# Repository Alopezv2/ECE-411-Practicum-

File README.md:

# ECE-411-Practicum-Skynet-2020

The Future in Artificial Intelligence 

The following Repo consits of the firmware, PCB layout, schematic and more
resources used to build and complete the project.

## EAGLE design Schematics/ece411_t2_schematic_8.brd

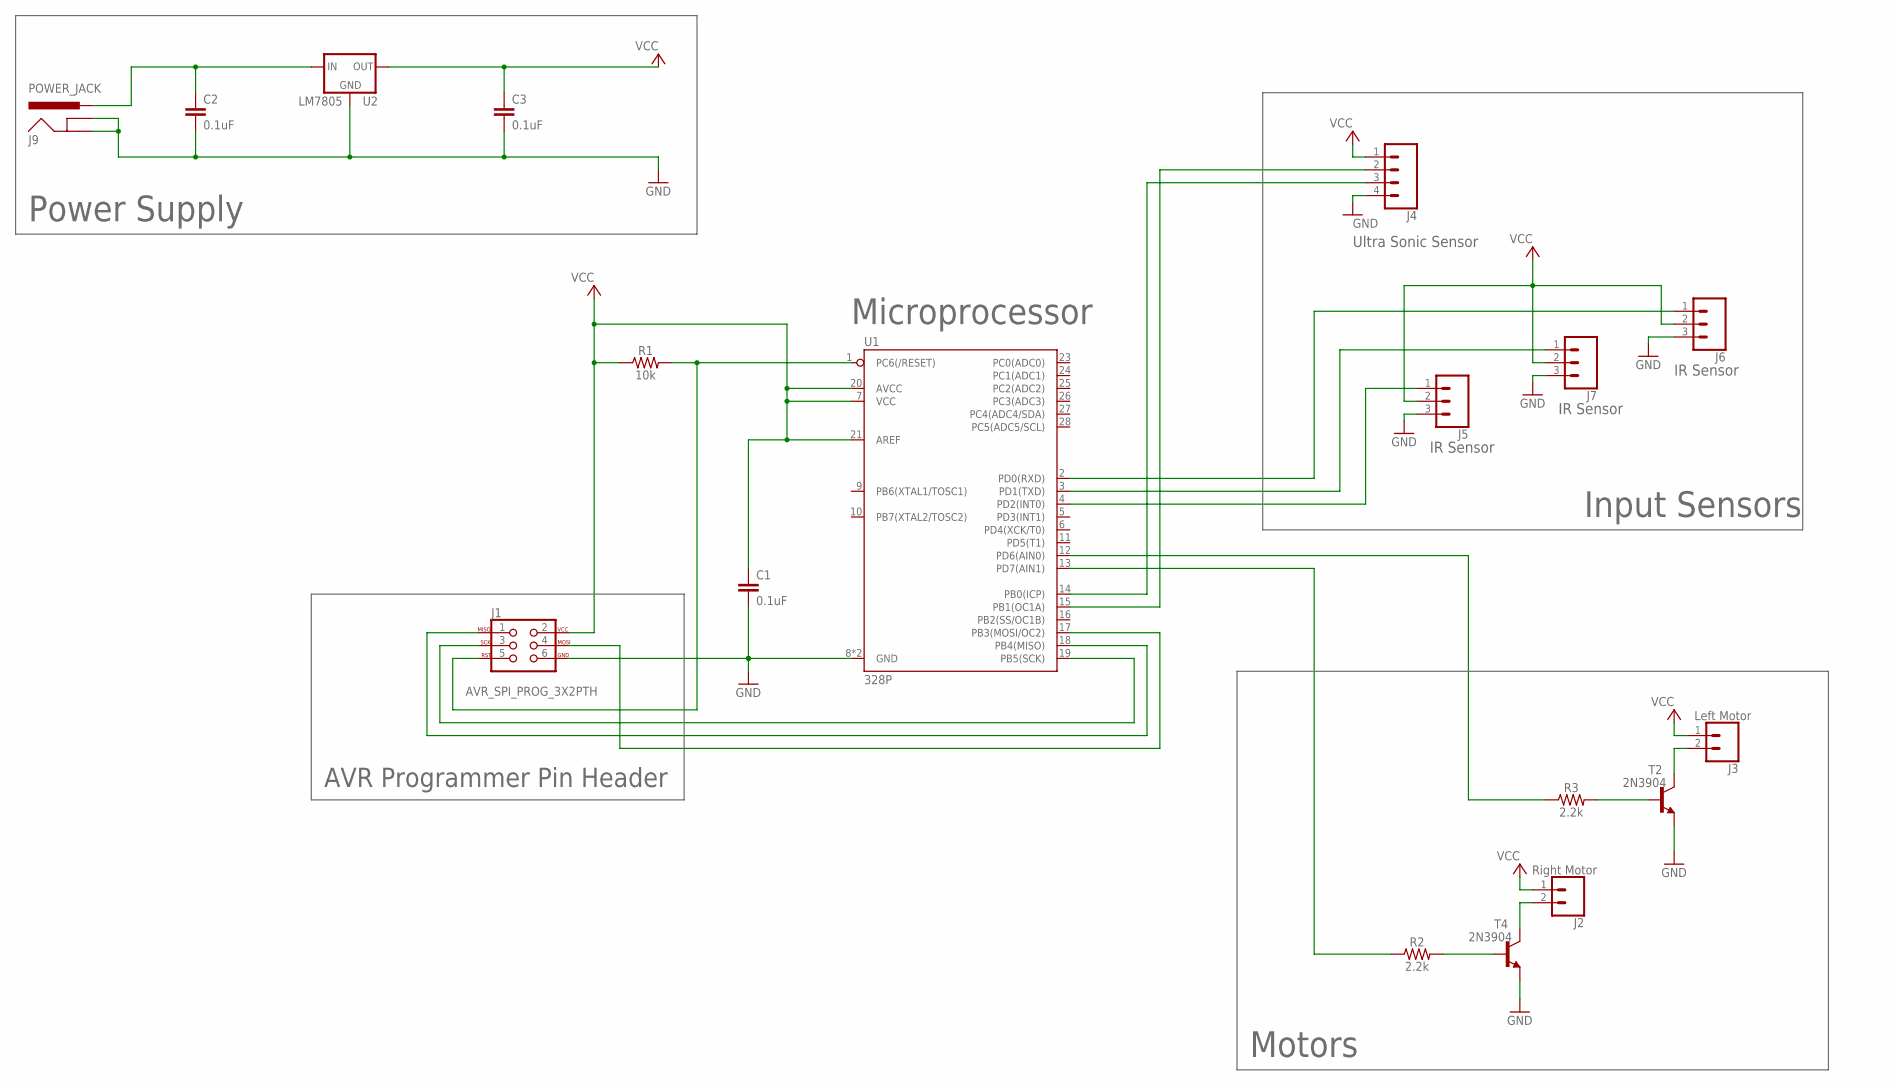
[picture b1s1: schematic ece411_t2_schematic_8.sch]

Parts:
C1, C2, C3: 0.1uF; 0402
J1: AVR_SPI_PROG_3X2PTH; 2X3
J2: Right Motor; 1X02
J3: Left Motor; 1X02
J4: CONN_04; 1X04
J5, J6, J7: 455-1750-1-ND; 1X03
J9: POWER_JACK; POWER_JACK_PTH
R1: 10k; 0402
R2, R3: 2.2k; 0603
T2, T4: 2N3904; TO92
U1: 328P; DIP28
U2: LM7805; TO-220-ALT

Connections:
GND: C1.2, C2.2, C3.2, J1.6, J4.4, J5.3, J6.3, J7.3, J9.GND, J9.GNDBREAK, T2.3 (E), T4.3 (E), U1.8 (GND), U1.22 (GND), U2.GND
MOSI: J1.4, U1.17 (PB3(MOSI/OC2))
unnamed: R3.1, U1.12 (PD6(AIN0))
unnamed: J3.2, T2.1 (C)
unnamed: R2.2, T4.2 (B)
unnamed: R3.2, T2.2 (B)
unnamed: J1.1, U1.18 (PB4(MISO))
unnamed: J2.2, T4.1 (C)
unnamed: J5.1, U1.4 (PD2(INT0))
unnamed: J7.1, U1.3 (PD1(TXD))
unnamed: J6.1, U1.2 (PD0(RXD))
unnamed: J1.5, R1.2, U1.1 (PC6(/RESET))
unnamed: J4.2, U1.15 (PB1(OC1A))
unnamed: J4.3, U1.14 (PB0(ICP))
unnamed: R2.1, U1.13 (PD7(AIN1))
SCK: J1.3, U1.19 (PB5(SCK))
VCC: C1.1, C3.1, J1.2, J2.1, J3.1, J4.1, J5.2, J6.2, J7.2, R1.1, U1.7 (VCC), U1.20 (AVCC), U1.21 (AREF), U2.OUT
VIN: C2.1, J9.PWR, U2.IN

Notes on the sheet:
Motors
Input Sensors
IR Sensor
Power Supply
AVR Programmer Pin Header
Microprocessor
Ultra Sonic Sensor

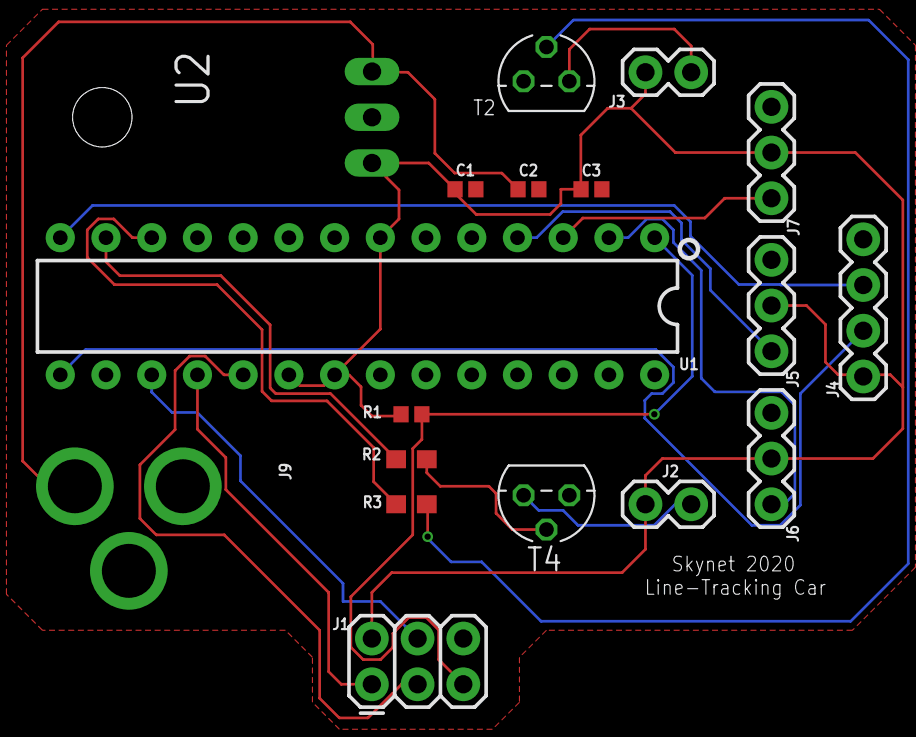
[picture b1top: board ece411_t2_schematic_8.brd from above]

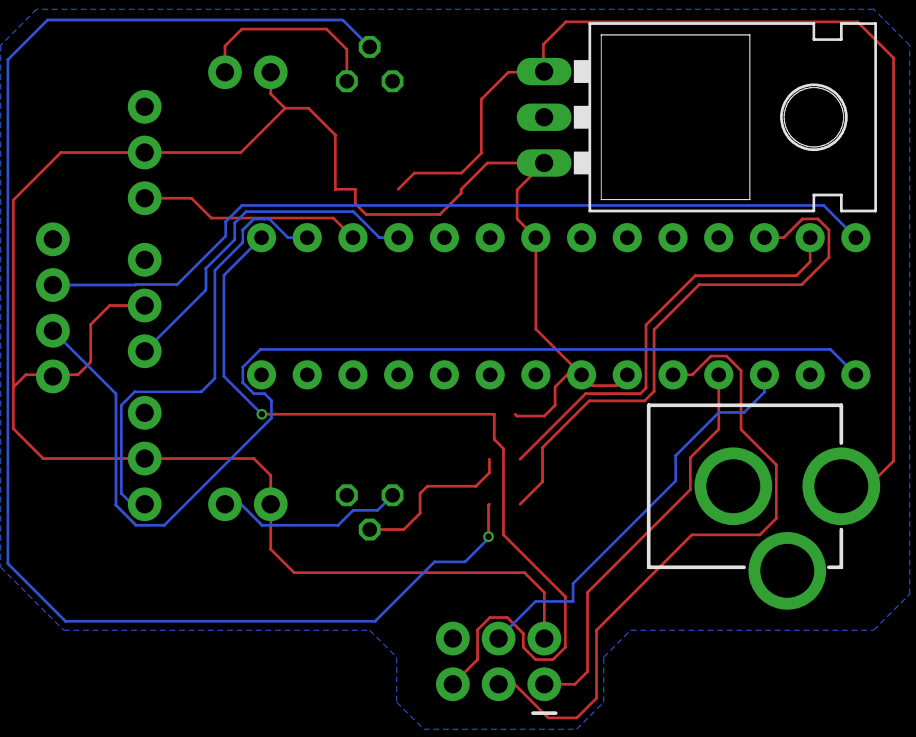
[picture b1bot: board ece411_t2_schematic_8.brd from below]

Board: 2 copper layers, 18 parts (2 on the bottom side), 18 nets.

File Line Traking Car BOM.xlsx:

Qty | Parts | MFR | MPN | Description
1.0 | U1 | Microchip Technology | ATMEGA328P_PDIP | IC MCU 8BIT 32KB FLASH 28DIP
1.0 | J1 | Adafruit Industries LLC | 1465.0 | AVR ISP 6 Pin, ATMEGA328 Programer
4.0 | T1, T2, T3, T4 | STMicroelectronis | 2N3904 | NPN TRANSISTOR
2.0 | J2,J3 | Sparkfun | CONN_02 | Multi connection point. Often used as Generic Header-pin footprint for 0.1 inch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
3.0 | J4,J5,J6 | Sparkfun | CONN_03 | Multi connection point. Often used as Generic Header-pin footprint for 0.1 inch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
1.0 | J7 | Sparkfun | CONN_04 | Multi connection point. Often used as Generic Header-pin footprint for 0.1 inch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
1.0 | T5 | STMicroelectronics | LM7809CT | Positive Voltage Regulator
3.0 | T6, T7, T8 | Samsung Electro-Mechanics | CL05A104KA5NNN | Cerimaic .1uF Capacitor

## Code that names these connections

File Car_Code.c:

/*
 * ultrasonic.c
 *
 * Created: 11/20/2020
 * Author: Alan Gonzalez
 */ 
#define _NOP() do { __asm__ __volatile__ ("nop"); } while(0)
#define F_CPU 1000000UL

#include <avr/io.h>
#include "capt_timer.h"

int tick_count = 0;								// to count how many times the timer has ran
int t1_ticks = 0;								// to count how many ticks the echo pin was high for
int car_on = 1;

void init_input_capt_timer() {
	TIMSK1 |= (1 << ICIE1);						// enable input capture interrupts on timer1
	TCCR1B |= (1 << ICES1) | (1 << ICNC1) | (1 << CS12);
	/* enable rising edge detection
	 * noise cancellation
	 * clock pre-scaler 256
	 */
	edge.current_edge = RISING;
	edge.next_edge = RISING;
}

void init_timer2() {
	OCR2A = (uint8_t) OCR2A_VALUE;				// set the timer2 to generate interrupt every 20us
	TIFR2 |= (1 << OCF2A);						// clear the output compare match flag
	TCCR2A |= (1 << WGM21);						// set timer2 to CTC mode
	TIMSK2 |= (1 << OCIE2A);					// enable timer2 compare match interrupts
	TCCR2B |= (1 << CS21);						// set timer2 clock prescaler to 8 and start timer
}

int main(void)
{

    DDRB &= ~(1 << PB0);						// Set PB0 (pin 14) to input for Echo
    DDRB |= (1 << PB1);							// Set PB1 (pin 15) to output for Trigger
	DDRD |= (1 << PD2);							// Set PD2 (pin 4) to output for LED
	DDRD |= (1 << PD6) | (1 << PD7);			// set Pin.7 and Pin.6 as outputs
	
	t1_ticks = 0;								// to count how many ticks the echo pin was high for
	car_on = 1;
	
	init_input_capt_timer();					// initialize timer1
	init_timer2();								// initialize timer2
	
	sei();										// enable interrupts

	while (1)
	{
			_NOP();								// wait for interrupt
			
			
			}


}

ISR(TIMER1_CAPT_vect)
{
	cli();										// disable interrupts
	
	switch(edge.next_edge) {
	case RISING: {
		TCNT1 = 0;								// start the timer1 counter at 0
		TCCR1B &= ~(1 << ICES1);				// next interrupt on falling edge
		edge.current_edge = RISING;
		edge.next_edge = FALLING;
	}
		break;
	
	case FALLING: {
		t1_ticks = (uint16_t) ICR1L;
		t1_ticks |= (uint16_t) (ICR1H << 8);	// store number of ticks between rising and falling edge
		TCCR1B |= (1 << ICES1);					// next interrupt on rising edge
		edge.current_edge = FALLING;
		edge.next_edge = RISING;
		if(t1_ticks > 0 && t1_ticks < 8) {
			//////////////////////////////////////////////////////
			// what will it do when it gets too close to obstacle?
			
			//PORTD |= (1 << PORTD2);			// turn LED on TEST
			car_on = 0;							// turn the car off
			PORTD &= ~(1 << PD6);				// clear PORTD.6 (RIGHT MOTOR OFF)
			PORTD &= ~(1 << PD7);				// clear PORTD.7 (LEFT MOTOR OFF)
			//////////////////////////////////////////////////////
		}
		else
		car_on = 1;								// turn the car on
	}
		break;
		
	default:
		break;
	}
	sei();										// enable interrupts
}

ISR(TIMER2_COMPA_vect) {
	cli();										// disable interrupts
	tick_count++;
	
	if(car_on) {
	// get input from PinD0 (IR SENSOR) and output to PinD6 (MOTOR)
	if((PIND & 0x01) != 0)						// read PIND.0
	PORTD &= ~(1 << PD6);						// clear PORTD.6
	else
	PORTD |= (1 << PD6);						// set PORTD.6
	
	// get input from PinD1 (IR SENSOR) and output to PinD7 (MOTOR)
	if((PIND & 0x02) != 0)						// read PIND.1
	PORTD &= ~(1 << PD7);						// clear PORTD.7
	else
	PORTD |= (1 << PD7);						// set PORTD.7	
	}

	if (tick_count == 1) {
		PORTB |= (1 << PB1);					// set ULTRASONIC Trigger pin to HIGH
	}
	
	if (tick_count == 2) {
		PORTB &= ~(1 << PB1);					// clear ULTRASONIC Trigger pin to LOW
	}
	
	if (tick_count == 1500) {
		tick_count = 0;							// reset the timer to set the trigger pin again
		//PORTD &= ~(1 << PORTD2);				// turn LED off TEST
	}
	
	sei();
}
	

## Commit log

2020-11-12 Add files via upload
    First draft of the BOM
2020-11-17 Create PCB & Schematic Team Review
2020-11-17 Update PCB & Schematic Team Review
2020-11-19 Add files via upload
    Final Schematic with no dimension and clearance errors.
2020-12-09 Create Schematic_1
2020-12-09 Rename ece411_t2_schematic.sch to Schematic/ece411_t2_schematic.sch
2020-12-09 Rename ece411_t2_schematic_11_15.brd to Schematics/ece411_t2_schematic_11_15.brd
2020-12-09 Rename Schematic/ece411_t2_schematic.sch to Schematics/ece411_t2_schematic.sch
2020-12-09 Update and rename Schematic_1 to Ghost File
2020-12-09 Rename ece411_t2_schematic_11_15.sch to Schematics/ece411_t2_schematic_11_15.sch
2020-12-09 Rename ece411_t2_schematic_3.sch to Schematics/ece411_t2_schematic_3.sch
2020-12-09 Rename ece411_t2_schematic_4.brd to Schematics/ece411_t2_schematic_4.brd
2020-12-09 Rename ece411_t2_schematic_4.sch to Schematics/ece411_t2_schematic_4.sch
2020-12-09 Rename ece411_t2_schematic_5.brd to Schematics/ece411_t2_schematic_5.brd
2020-12-09 Rename ece411_t2_schematic_5.sch to Schematics/ece411_t2_schematic_5.sch
2020-12-09 Rename ece411_t2_schematic_6.brd to Schematics/ece411_t2_schematic_6.brd
2020-12-09 Rename ece411_t2_schematic_6.sch to Schematics/ece411_t2_schematic_6.sch
2020-12-09 Rename ece411_t2_schematic_7.brd to Schematics/ece411_t2_schematic_7.brd
2020-12-09 Rename ece411_t2_schematic_7.sch to Schematics/ece411_t2_schematic_7.sch
2020-12-09 Rename ece411_t2_schematic_8.brd to Schematics/ece411_t2_schematic_8.brd
2020-12-09 Rename ece411_t2_schematic_8.sch to Schematics/ece411_t2_schematic_8.sch
2020-12-09 Rename ece411_t2_schematic_9.brd to Schematics/ece411_t2_schematic_9.brd
2020-12-09 Rename ece411_t2_schematic_FINAL.brd to Schematics/ece411_t2_schematic_FINAL.brd
2020-12-09 Rename ece411_t2_schematic_FINAL.sch to Schematics/ece411_t2_schematic_FINAL.sch
2020-12-09 Update Ghost File
2020-12-09 Rename Ghost File to Schematics
2020-12-09 Create Firmware
2020-12-09 Rename Car_Code.c to Firmware/Car_Code.c
2020-12-09 Rename IR sensor.c to Firmware/IR_sensor.c
2020-12-09 Rename ultrasonic.c to Firmware/ultrasonic.c
2020-12-09 Rename capt_timer.h to Firmware/capt_timer.h
2020-12-09 Rename PCB & Schematic Team Review to Schematics/PCB & Schematic Team Review

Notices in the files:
parts and their libraries:
SparkFun-Capacitors: Licensing: Creative Commons ShareAlike 4.0 International - https://creativecommons.org/licenses/by-sa/4.0
